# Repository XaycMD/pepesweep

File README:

# Pepesweep
20 keys wireless keyboard based on the Sweep. Layout inspired by Ben Vallack's ThePiano

## Layout

## Pics

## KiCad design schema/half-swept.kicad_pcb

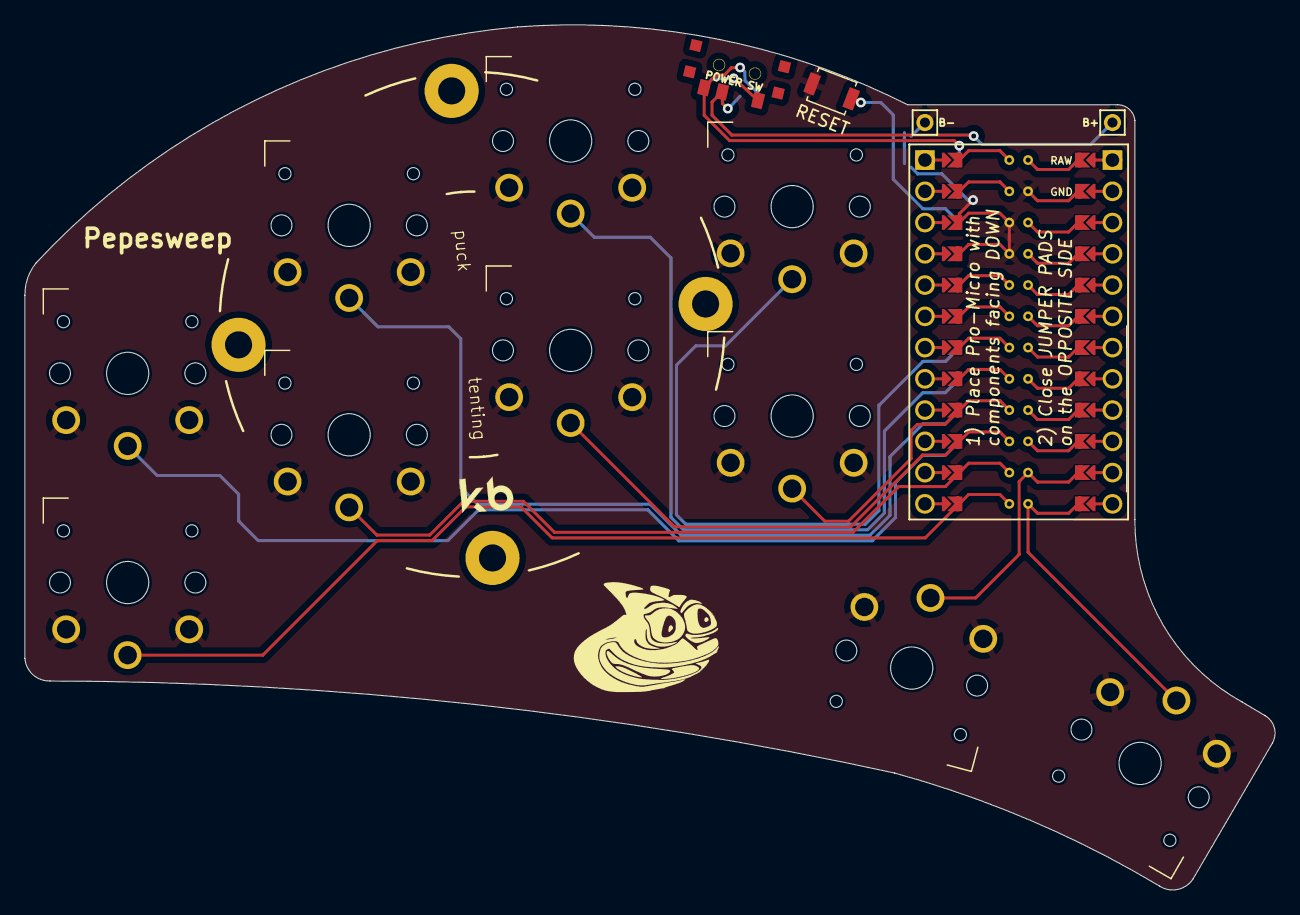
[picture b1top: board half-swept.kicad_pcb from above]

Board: 2 copper layers, 101.6 x 70.3 mm, 15 parts (0 on the bottom side), 14 nets.

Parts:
B+: MountingHole_Pad; 1pin_conn
B-: MountingHole_Pad; 1pin_conn
POWER SW: SW_SPDT; SPDT_C128955
RSW2: SW_Push; Tactile-Switch_SMT
SW1, SW2, SW3, SW4, SW5, SW6, SW7, SW8, SW9, SW10: SW_Push; SW_PG1350_rev_DPB
U1: ProMicro-kbd; ProMicro_jumpers_facedown

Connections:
BT+_r: B+.1, POWER SW.2
Switch1: SW7.1, U1.10
Switch2: SW3.1, U1.17
Switch3: SW4.1, U1.18
Switch6: SW2.1, U1.16
Switch7: SW1.1, U1.15
Switch8: SW9.1, U1.14
Switch9: SW10.1, U1.13
Switch15: SW8.1, U1.9
Switch16: SW6.1, U1.11
Switch17: SW5.1, U1.12
gnd: B-.1, RSW2.1, RSW2.2, SW1.2, SW2.2, SW3.2, SW4.2, SW5.2, SW6.2, SW7.2, SW8.2, SW9.2, SW10.2, U1.3, U1.4, U1.23
raw: POWER SW.3, U1.24
reset: RSW2.1, RSW2.2, U1.22

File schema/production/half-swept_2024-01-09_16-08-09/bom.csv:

Designator,Footprint,Quantity,Value,LCSC Part #
"B+, B-",1pin_conn,2,MountingHole_Pad,
POWER SW,SPDT_C128955,1,SW_SPDT,
RSW2,Tactile-Switch_SMT,1,SW_Push,
"SW1, SW10, SW2, SW3, SW4, SW5, SW6, SW7, SW8, SW9",SW_PG1350_rev_DPB,10,SW_Push,
U1,ProMicro_jumpers_facedown,1,ProMicro-kbd,

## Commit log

2023-11-08 init
2023-11-08 try layout
2023-11-08 swap pins
2023-11-08 mirror right half
2023-11-08 new keymap
2023-11-08 swap o and c
2023-11-08 remove
2023-11-08 swap a and i
2023-11-12 move Y to 2 layer
2024-01-17 add gerber
2024-02-28 new pinout
2024-02-28 rename
2024-02-28 add reset
2024-02-28 change pinout
2024-02-28 build puni again
2024-03-03 add schema
2024-03-06 add photos
2024-03-06 Rename README to README.md
2024-03-06 cleanup
2024-03-18 add taipo
2024-03-18 remove shortcuts
2024-03-18 add layers for default combo
2024-03-18 fix and add tests
2024-03-18 change config
2024-03-18 changed
2024-03-19 decreased timeout
2024-03-19 swap ctrl and shift
2024-03-19 increase timeout, add ctrl s
2024-03-20 decrease timeout
2024-04-16 remove taipo
2024-04-16 remove taipo include
